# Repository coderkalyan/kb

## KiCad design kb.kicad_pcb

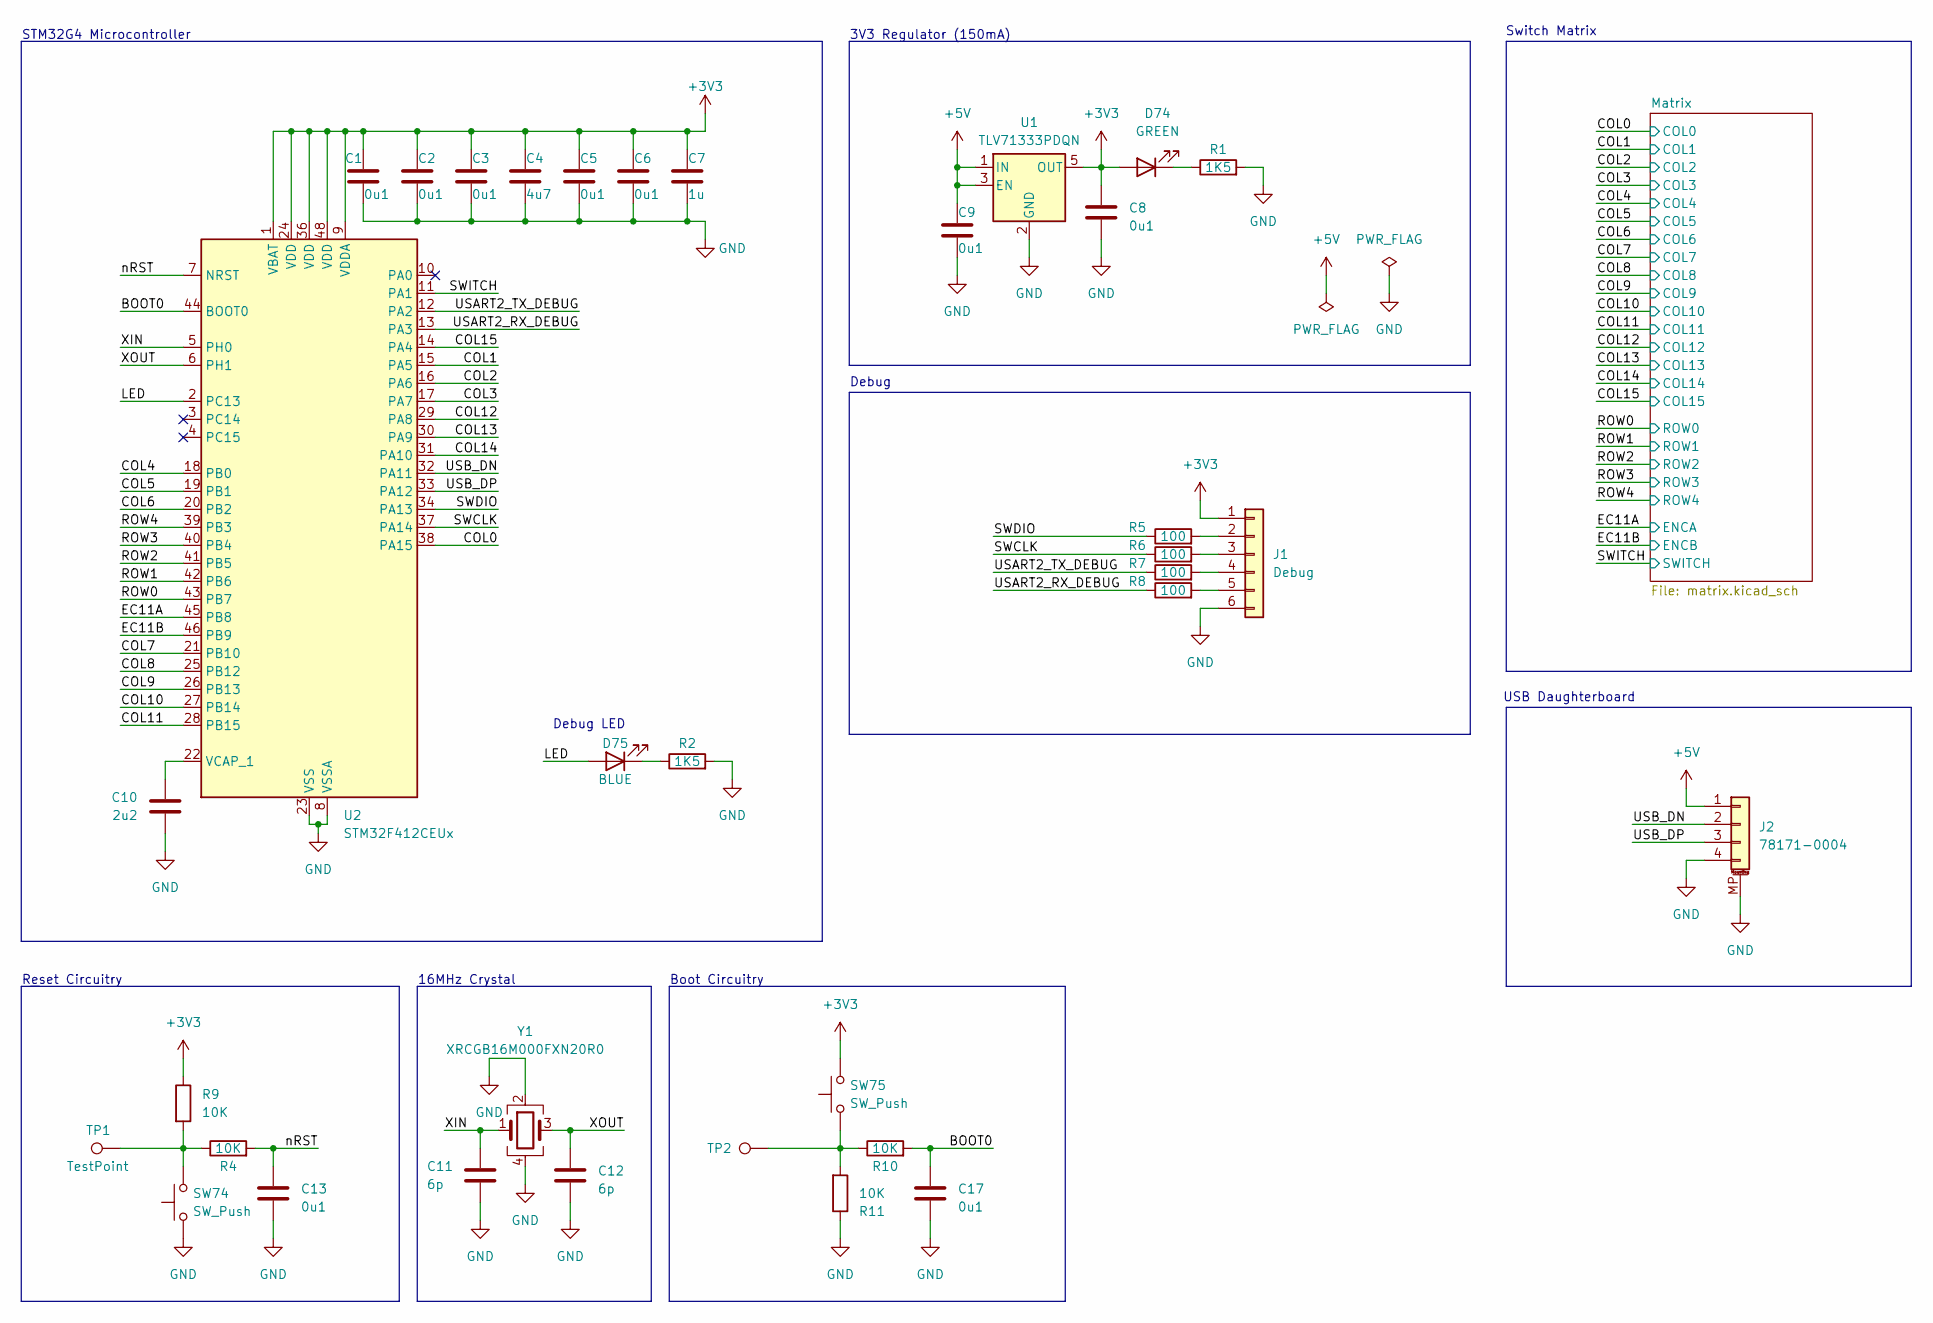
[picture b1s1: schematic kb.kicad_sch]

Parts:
C1, C2, C3, C5, C6, C13, C17: 0u1; C_0603_1608Metric; LCSC C907967
C4: 4u7; C_0603_1608Metric; LCSC C253012
C7: 1u; C_0603_1608Metric; LCSC C5142562
C8, C9: 0u1; C_0603_1608Metric; LCSC C282519
C10: 2u2; C_0603_1608Metric; LCSC C253012
C11, C12: 6p; C_0402_1005Metric; LCSC C466231
D74: GREEN; LED_0402_1005Metric; Part QBLP595-IG; LCSC C2856703
D75: BLUE; LED_0402_1005Metric
J1: Debug; PinHeader_1x06_P2.54mm_Horizontal
J2: 78171-0004; Molex_Pico-EZmate_78171-0004_1x04-1MP_P1.20mm_Vertical
R1: 1K5; R_0603_1608Metric; LCSC C25930
R2: 1K5; R_0603_1608Metric
R4, R9: 10K; R_0603_1608Metric; LCSC C102690
R5, R6, R7: 100; R_0603_1608Metric
R8: 100; R_0603_1608Metric; LCSC C102690
R10: 10K; R_0603_1608Metric; LCSC C3152018
R11: 10K; R_0603_1608Metric; LCSC C25531
SW74, SW75: SW_Push; SW_SPST_PTS810
TP1, TP2: TestPoint; TestPoint_Pad_1.0x1.0mm
U1: TLV71333PDQN; SOT-23-5; LCSC C2867340
U2: STM32F412CEUx; QFN-48-1EP_7x7mm_P0.5mm_EP5.6x5.6mm
Y1: XRCGB16M000FXN20R0; Crystal_SMD_2016-4Pin_2.0x1.6mm; Part XRCGB16M000FXN20R0; LCSC C907977

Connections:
+3V3: C1.1, C2.1, C3.1, C4.1, C5.1, C6.1, C7.1, C8.1, D74.2 (A), J1.1, R9.1, SW75.2, U1.5 (OUT), U2.1 (VBAT), U2.9 (VDDA), U2.24 (VDD), U2.36 (VDD), U2.48 (VDD); also elsewhere on the board
+5V: C9.1, J2.1, U1.1 (IN), U1.3 (EN)
/BOOT0: C17.1, R10.2, U2.44 (BOOT0)
/COL0: U2.38 (PA15); also elsewhere on the board
/COL1: U2.15 (PA5); also elsewhere on the board
/COL2: U2.16 (PA6); also elsewhere on the board
/COL3: U2.17 (PA7); also elsewhere on the board
/COL4: U2.18 (PB0); also elsewhere on the board
/COL5: U2.19 (PB1); also elsewhere on the board
/COL6: U2.20 (PB2); also elsewhere on the board
/COL7: U2.21 (PB10); also elsewhere on the board
/COL8: U2.25 (PB12); also elsewhere on the board
/COL9: U2.26 (PB13); also elsewhere on the board
/COL10: U2.27 (PB14); also elsewhere on the board
/COL11: U2.28 (PB15); also elsewhere on the board
/COL12: U2.29 (PA8); also elsewhere on the board
/COL13: U2.30 (PA9); also elsewhere on the board
/COL14: U2.31 (PA10); also elsewhere on the board
/COL15: U2.14 (PA4); also elsewhere on the board
/EC11A: U2.45 (PB8); also elsewhere on the board
/EC11B: U2.46 (PB9); also elsewhere on the board
/LED: D75.2 (A), U2.2 (PC13)
/ROW0: U2.43 (PB7); also elsewhere on the board
/ROW1: U2.42 (PB6); also elsewhere on the board
/ROW2: U2.41 (PB5); also elsewhere on the board
/ROW3: U2.40 (PB4); also elsewhere on the board
/ROW4: U2.39 (PB3); also elsewhere on the board
/SWCLK: R6.1, U2.37 (PA14)
/SWDIO: R5.1, U2.34 (PA13)
/SWITCH: U2.11 (PA1); also elsewhere on the board
/USART2_RX_DEBUG: R8.1, U2.13 (PA3)
/USART2_TX_DEBUG: R7.1, U2.12 (PA2)
/USB_DN: J2.2, U2.32 (PA11)
/USB_DP: J2.3, U2.33 (PA12)
/XIN: C11.1, U2.5 (PH0), Y1.1
/XOUT: C12.1, U2.6 (PH1), Y1.3
/nRST: C13.1, R4.2, U2.7 (NRST)
unnamed: D74.1 (K), R1.1
unnamed: D75.1 (K), R2.1
unnamed: J1.2, R5.2
unnamed: J1.3, R6.2
unnamed: J1.4, R7.2
unnamed: J1.5, R8.2
unnamed: R4.1, R9.2, SW74.2, TP1.1
unnamed: R10.1, R11.2, SW75.1, TP2.1
unnamed: C10.1, U2.22 (VCAP_1)

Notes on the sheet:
Reset Circuitry
Debug LED
3V3 Regulator (150mA)
16MHz Crystal
STM32G4 Microcontroller
USB Daughterboard
Boot Circuitry
Switch Matrix
Debug

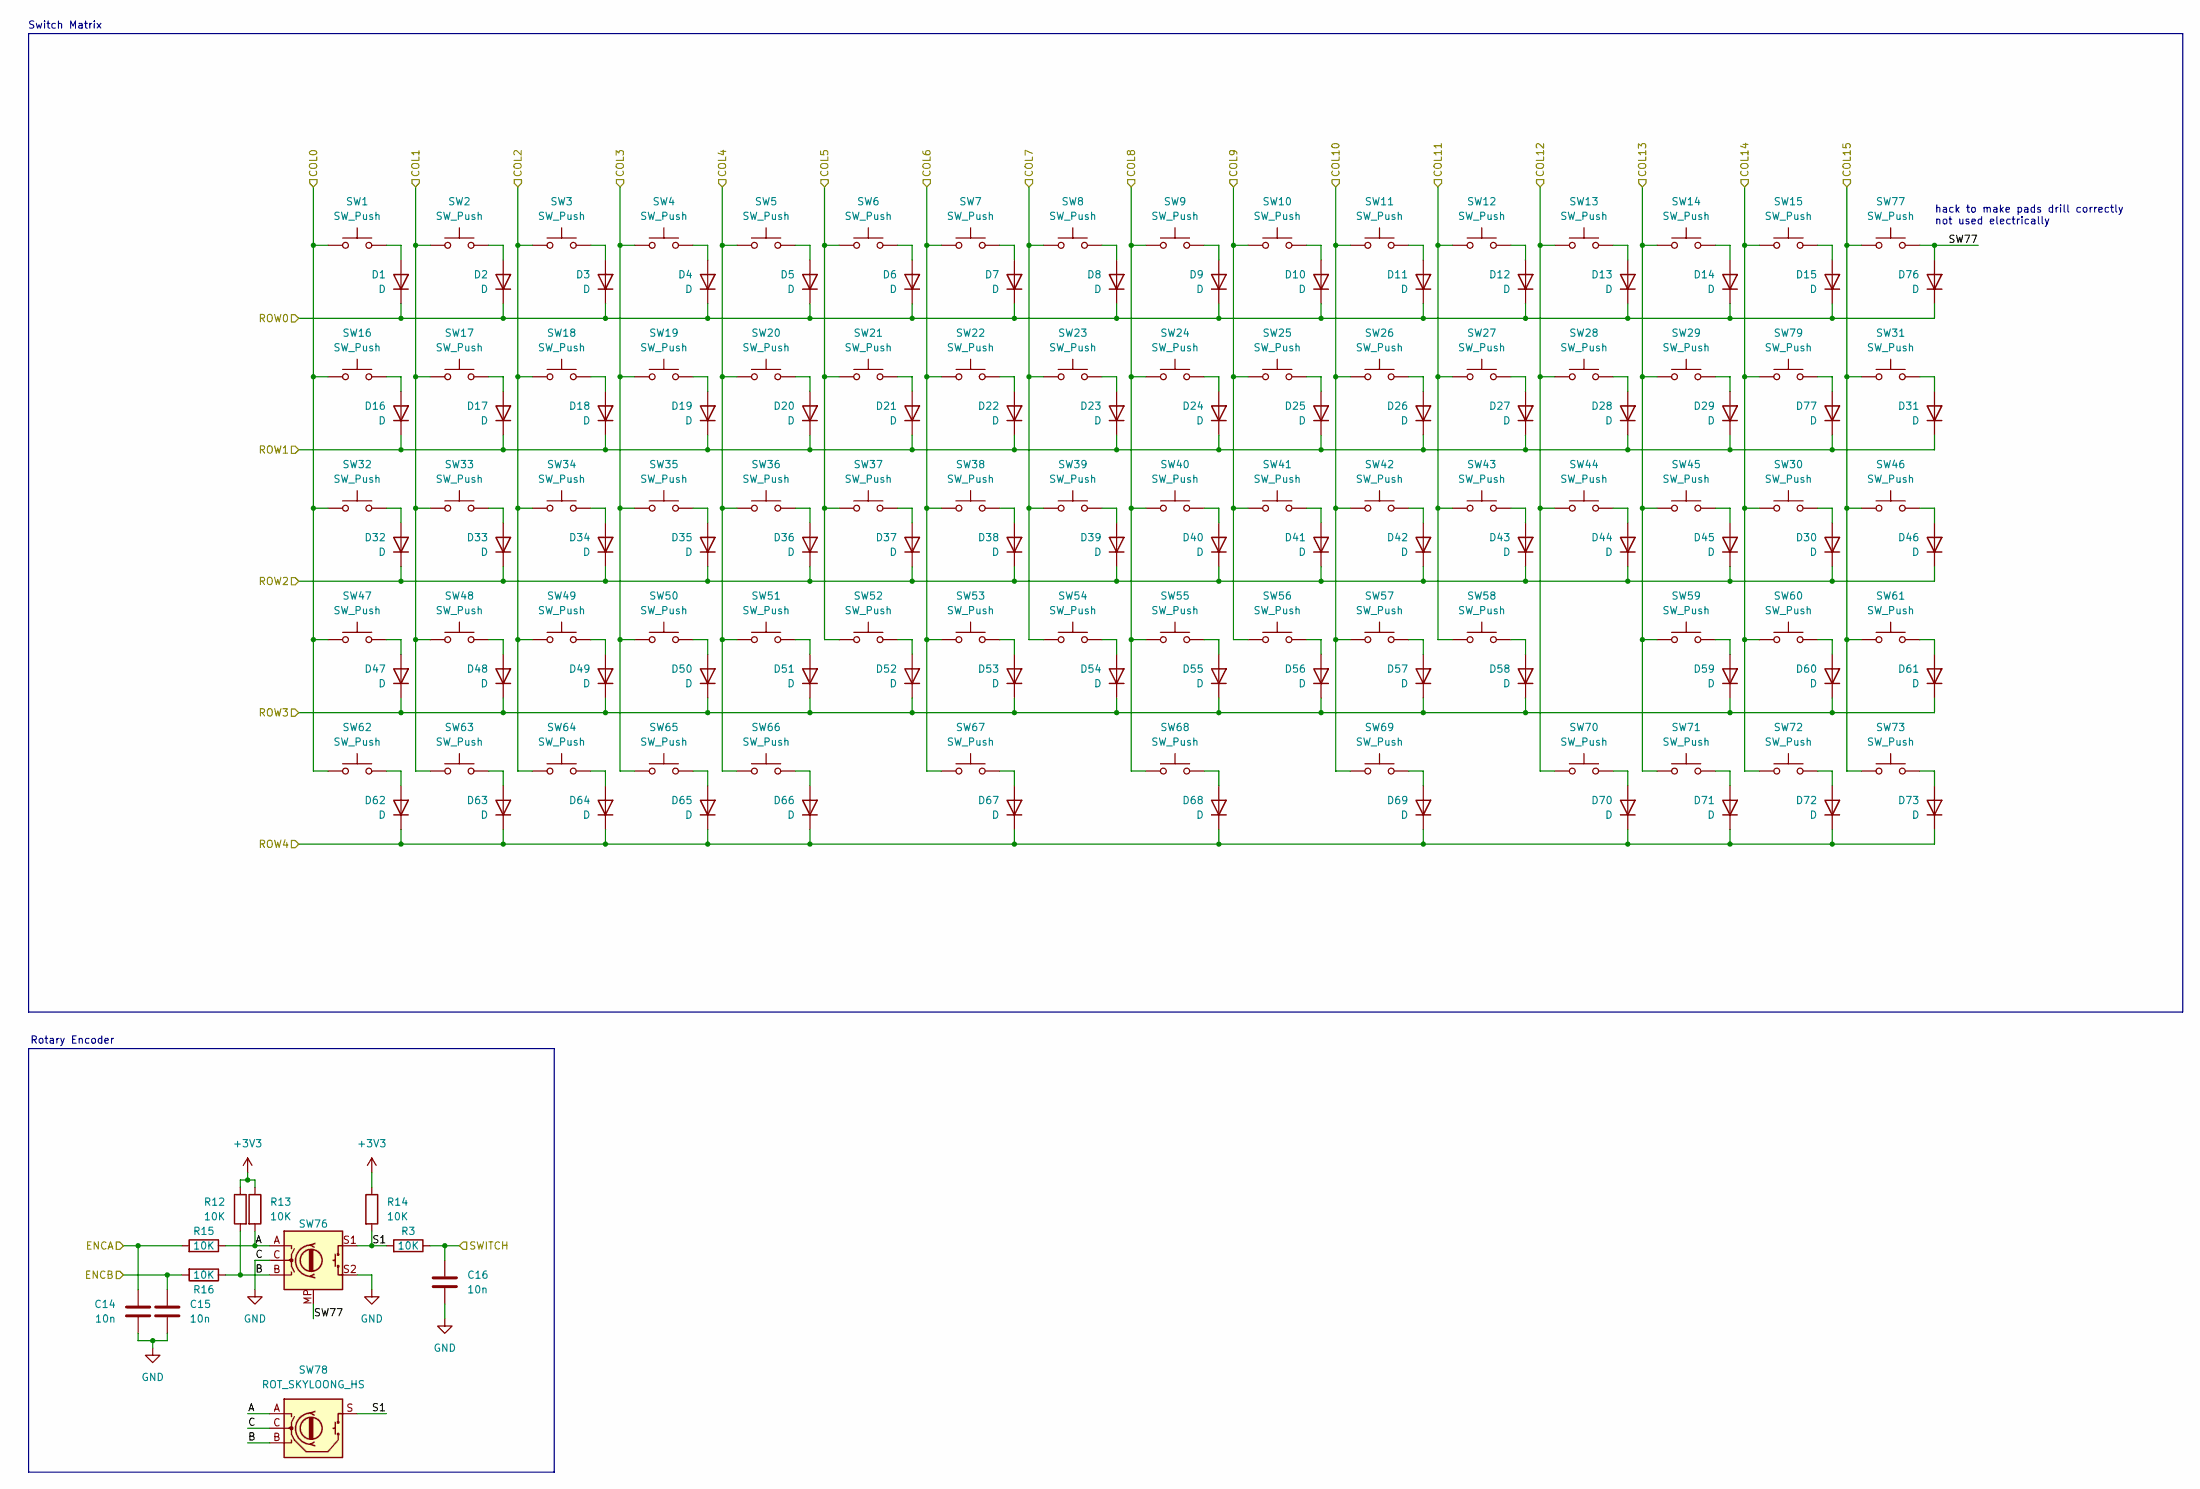
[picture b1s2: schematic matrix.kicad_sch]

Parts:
C14: 10n; C_0603_1608Metric; LCSC C907967
C15, C16: 10n; C_0603_1608Metric; LCSC C466231
D1, D2, D3, D4, D5, D6, D7, D8, D9, D10, D11, D12, D13, D14, D15, D16, D17, D18, D19, D20, D21, D22, D23, D24, D25, D26, D27, D28, D29, D30, D31, D32, D33, D34, D35, D36, D37, D38, D39, D40, D41, D42, D43, D44, D45, D46, D47, D48, D49, D50, D51, D52, D53, D54, D55, D56, D57, D58, D59, D60, D61, D62, D63, D64, D65, D66, D67, D68, D69, D70, D71, D72, D73, D76, D77: D; D_SOD-123
R3, R13, R14, R15, R16: 10K; R_0603_1608Metric
R12: 10K; R_0603_1608Metric; LCSC C25930
SW1, SW2, SW3, SW4, SW5, SW6, SW7, SW8, SW9, SW10, SW11, SW12, SW13, SW14, SW15, SW16, SW18, SW19, SW20, SW21, SW22, SW23, SW24, SW25, SW26, SW27, SW28, SW29, SW31, SW32, SW34, SW35, SW36, SW37, SW38, SW39, SW40, SW41, SW42, SW43, SW44, SW45, SW46, SW47, SW48, SW49, SW50, SW51, SW52, SW53, SW54, SW55, SW56, SW57, SW58, SW60, SW61, SW62, SW66, SW68, SW71, SW72, SW73, SW77, SW79: SW_Push; SW_MX_1u
SW17, SW30, SW69, SW70: SW_Push; SW_MX_1.5u
SW33, SW59, SW67: SW_Push; SW_MX_1.75u
SW63, SW64, SW65: SW_Push; SW_MX_1.25u
SW76: RotaryEncoder_Switch; ROT_Alps_EC11E-Switch
SW78: ROT_SKYLOONG_HS; ROT_SKYLOONG_HS-Switch

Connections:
+3V3: R12.1, R13.1, R14.1; also elsewhere on the board
/COL0: SW1.1, SW16.1, SW32.1, SW47.1, SW62.1; also elsewhere on the board
/COL1: SW2.1, SW17.1, SW33.1, SW48.1, SW63.1; also elsewhere on the board
/COL2: SW3.1, SW18.1, SW34.1, SW49.1, SW64.1; also elsewhere on the board
/COL3: SW4.1, SW19.1, SW35.1, SW50.1, SW65.1; also elsewhere on the board
/COL4: SW5.1, SW20.1, SW36.1, SW51.1, SW66.1; also elsewhere on the board
/COL5: SW6.1, SW21.1, SW37.1, SW52.1; also elsewhere on the board
/COL6: SW7.1, SW22.1, SW38.1, SW53.1, SW67.1; also elsewhere on the board
/COL7: SW8.1, SW23.1, SW39.1, SW54.1; also elsewhere on the board
/COL8: SW9.1, SW24.1, SW40.1, SW55.1, SW68.1; also elsewhere on the board
/COL9: SW10.1, SW25.1, SW41.1, SW56.1; also elsewhere on the board
/COL10: SW11.1, SW26.1, SW42.1, SW57.1, SW69.1; also elsewhere on the board
/COL11: SW12.1, SW27.1, SW43.1, SW58.1; also elsewhere on the board
/COL12: SW13.1, SW28.1, SW44.1, SW70.1; also elsewhere on the board
/COL13: SW14.1, SW29.1, SW45.1, SW59.1, SW71.1; also elsewhere on the board
/COL14: SW15.1, SW30.1, SW60.1, SW72.1, SW79.1; also elsewhere on the board
/COL15: SW31.1, SW46.1, SW61.1, SW73.1, SW77.1; also elsewhere on the board
/EC11A: C14.1, R15.2; also elsewhere on the board
/EC11B: C15.1, R16.2; also elsewhere on the board
/Matrix/A: R13.2, R15.1, SW76.A, SW78.A
/Matrix/S1: R3.2, R14.2, SW76.S1, SW78.S
/Matrix/SW77: D76.2 (A), SW76.MP, SW77.2
/ROW0: D1.1 (K), D2.1 (K), D3.1 (K), D4.1 (K), D5.1 (K), D6.1 (K), D7.1 (K), D8.1 (K), D9.1 (K), D10.1 (K), D11.1 (K), D12.1 (K), D13.1 (K), D14.1 (K), D15.1 (K), D76.1 (K); also elsewhere on the board
/ROW1: D16.1 (K), D17.1 (K), D18.1 (K), D19.1 (K), D20.1 (K), D21.1 (K), D22.1 (K), D23.1 (K), D24.1 (K), D25.1 (K), D26.1 (K), D27.1 (K), D28.1 (K), D29.1 (K), D31.1 (K), D77.1 (K); also elsewhere on the board
/ROW2: D30.1 (K), D32.1 (K), D33.1 (K), D34.1 (K), D35.1 (K), D36.1 (K), D37.1 (K), D38.1 (K), D39.1 (K), D40.1 (K), D41.1 (K), D42.1 (K), D43.1 (K), D44.1 (K), D45.1 (K), D46.1 (K); also elsewhere on the board
/ROW3: D47.1 (K), D48.1 (K), D49.1 (K), D50.1 (K), D51.1 (K), D52.1 (K), D53.1 (K), D54.1 (K), D55.1 (K), D56.1 (K), D57.1 (K), D58.1 (K), D59.1 (K), D60.1 (K), D61.1 (K); also elsewhere on the board
/ROW4: D62.1 (K), D63.1 (K), D64.1 (K), D65.1 (K), D66.1 (K), D67.1 (K), D68.1 (K), D69.1 (K), D70.1 (K), D71.1 (K), D72.1 (K), D73.1 (K); also elsewhere on the board
/SWITCH: C16.1, R3.1; also elsewhere on the board
unnamed: D1.2 (A), SW1.2
unnamed: D2.2 (A), SW2.2
unnamed: D3.2 (A), SW3.2
unnamed: D4.2 (A), SW4.2
unnamed: D5.2 (A), SW5.2
unnamed: D6.2 (A), SW6.2
unnamed: D7.2 (A), SW7.2
unnamed: D8.2 (A), SW8.2
unnamed: D9.2 (A), SW9.2
unnamed: D10.2 (A), SW10.2
unnamed: D11.2 (A), SW11.2
unnamed: D12.2 (A), SW12.2
unnamed: D13.2 (A), SW13.2
unnamed: D14.2 (A), SW14.2
unnamed: D15.2 (A), SW15.2
unnamed: D16.2 (A), SW16.2
unnamed: D17.2 (A), SW17.2
unnamed: D18.2 (A), SW18.2
unnamed: D19.2 (A), SW19.2
unnamed: D20.2 (A), SW20.2
unnamed: D21.2 (A), SW21.2
unnamed: D22.2 (A), SW22.2
unnamed: D23.2 (A), SW23.2
unnamed: D24.2 (A), SW24.2
unnamed: D25.2 (A), SW25.2
unnamed: D26.2 (A), SW26.2
unnamed: D27.2 (A), SW27.2
unnamed: D28.2 (A), SW28.2
unnamed: D29.2 (A), SW29.2
unnamed: D30.2 (A), SW30.2
unnamed: D31.2 (A), SW31.2
unnamed: D32.2 (A), SW32.2
unnamed: D33.2 (A), SW33.2
unnamed: D34.2 (A), SW34.2
unnamed: D35.2 (A), SW35.2
unnamed: D36.2 (A), SW36.2
unnamed: D37.2 (A), SW37.2
unnamed: D38.2 (A), SW38.2
unnamed: D39.2 (A), SW39.2
unnamed: D40.2 (A), SW40.2
unnamed: D41.2 (A), SW41.2
unnamed: D42.2 (A), SW42.2
unnamed: D43.2 (A), SW43.2
unnamed: D44.2 (A), SW44.2
unnamed: D45.2 (A), SW45.2
unnamed: D46.2 (A), SW46.2
unnamed: D47.2 (A), SW47.2
unnamed: D48.2 (A), SW48.2
unnamed: D49.2 (A), SW49.2
unnamed: D50.2 (A), SW50.2
unnamed: D51.2 (A), SW51.2
unnamed: D52.2 (A), SW52.2
unnamed: D53.2 (A), SW53.2
unnamed: D54.2 (A), SW54.2
unnamed: D55.2 (A), SW55.2
unnamed: D56.2 (A), SW56.2
unnamed: D57.2 (A), SW57.2
unnamed: D58.2 (A), SW58.2
unnamed: D59.2 (A), SW59.2
unnamed: D60.2 (A), SW60.2
unnamed: D61.2 (A), SW61.2
unnamed: D62.2 (A), SW62.2
unnamed: D63.2 (A), SW63.2
unnamed: D64.2 (A), SW64.2
unnamed: D65.2 (A), SW65.2
unnamed: D66.2 (A), SW66.2
unnamed: D67.2 (A), SW67.2
unnamed: D68.2 (A), SW68.2
unnamed: D69.2 (A), SW69.2
unnamed: D70.2 (A), SW70.2
unnamed: D71.2 (A), SW71.2
unnamed: D72.2 (A), SW72.2
unnamed: D73.2 (A), SW73.2
unnamed: D77.2 (A), SW79.2

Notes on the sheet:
Switch Matrix
hack to make pads drill correctly not used electrically
Rotary Encoder

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
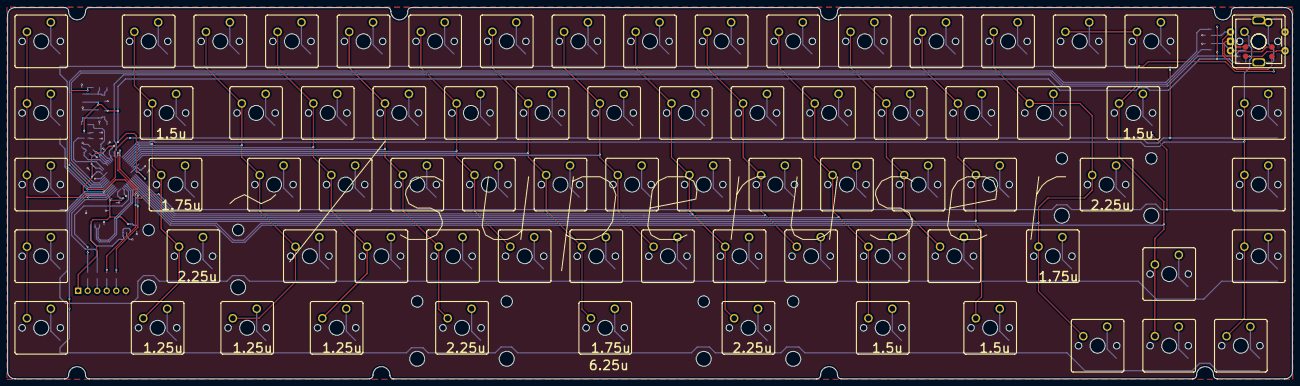
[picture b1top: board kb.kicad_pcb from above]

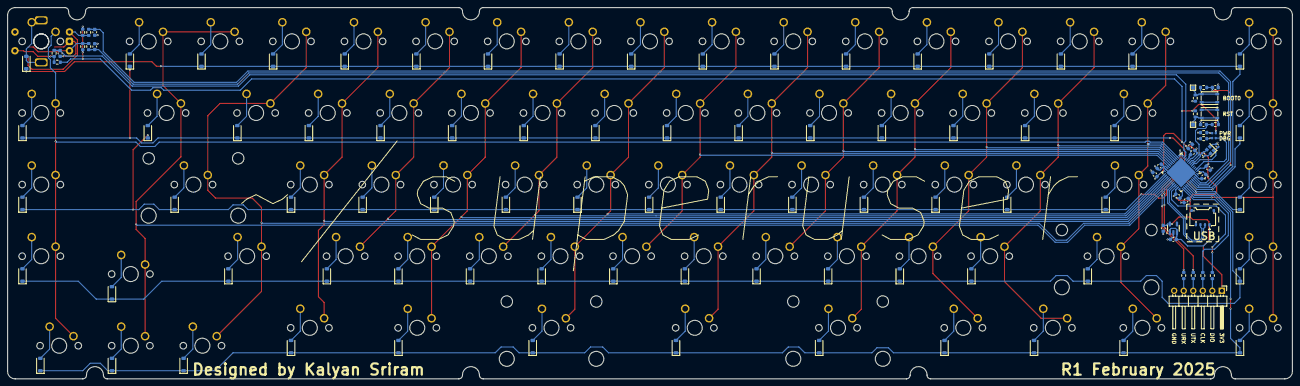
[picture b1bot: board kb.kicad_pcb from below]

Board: 2 copper layers, 341.8 x 98.8 mm, 196 parts (119 on the bottom side), 125 nets.

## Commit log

2024-04-18 update standard libs
2024-04-19 more schematics work
2025-01-26 update layout and switch to wired
2025-01-27 work on layout and routing
2025-01-28 more routing work
2025-02-14 backup before encoder fix
2025-02-14 fixed encoder
2025-02-17 final export
2025-02-19 split backspace
2025-03-07 final export of r1
